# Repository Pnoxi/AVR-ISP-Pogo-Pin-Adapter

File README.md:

# AVR-ISP-Pogo-Pin-Adapter

Documentation
--------------------

https://hackaday.io/project/165027-avr-isp-pogo-pin-adapters

Donate
--------------------

Do you like my work? [Let me know about it and support my other projects!](https://www.patreon.com/pnoxi)

Or just drink beer on my honor :wink:

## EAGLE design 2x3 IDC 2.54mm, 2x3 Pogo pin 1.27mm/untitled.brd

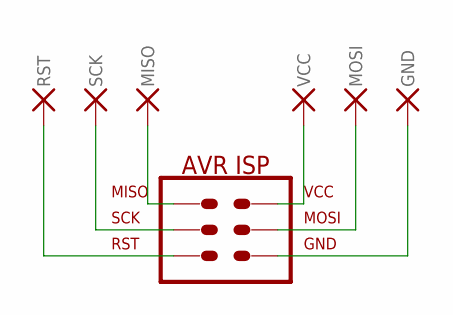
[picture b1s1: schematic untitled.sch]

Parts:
GND: GND; POGO_PIN_P50-XX_HORIZONTALLY
MISO: MISO; POGO_PIN_P50-XX_HORIZONTALLY
MOSI: MOSI; POGO_PIN_P50-XX_HORIZONTALLY
RST: RST; POGO_PIN_P50-XX_HORIZONTALLY
SCK: SCK; POGO_PIN_P50-XX_HORIZONTALLY
VCC: VCC; POGO_PIN_P50-XX_HORIZONTALLY
X1: AVR-ISP_6X_IDC_LOCK_EDGE_PCB; AVR-ISP-6_EDGE_PCB

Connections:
GND: GND.P$1, X1.GND
MISO: MISO.P$1, X1.MISO
MOSI: MOSI.P$1, X1.MOSI
RST: RST.P$1, X1.RST
SCK: SCK.P$1, X1.SCK
VCC: VCC.P$1, X1.VCC

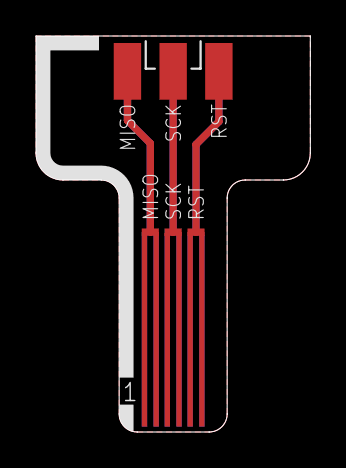
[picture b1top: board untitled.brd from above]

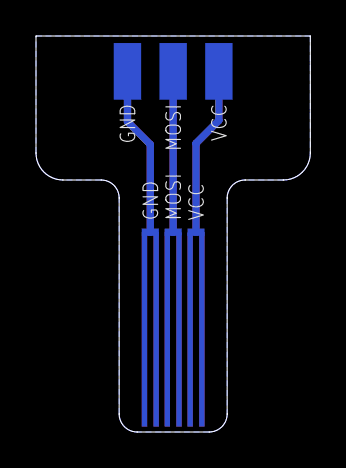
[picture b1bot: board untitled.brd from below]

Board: 2 copper layers, 15.2 x 22.0 mm, 8 parts (3 on the bottom side), 6 nets.

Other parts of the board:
U$1: 6.00X2.53

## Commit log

2019-04-15 Added Design Files!
2019-06-23 Added Documentation Link
